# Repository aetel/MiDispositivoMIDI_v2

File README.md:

# Warning
This repository is no loger active. Everything has been moved to the BanaNut Electronics repository:
https://github.com/bananutelectronics

# MiDispositivoMIDI_v2
MiDispositivoMIDI is a DIY MIDI Controller developed by a couple students of the Polytechnic University of Madrid for a workshop given in May and October of 2014. The code is under MIT license and the hardware is under CC BY-NC-SA 4.0. Everything can be downloaded from this repository. If you are interested in helping us to improve our proyect, let us know!

# https://www.facebook.com/midispositivomidi
# midispositivomidi@gmail.com

# Hardware License
<br /><span xmlns:dct="http://purl.org/dc/terms/" property="dct:title">MiDispositivoMIDI</span> by <a xmlns:cc="http://creativecommons.org/ns#" href="https://github.com/midispositivomidi" property="cc:attributionName" rel="cc:attributionURL">Alvaro Lopez Revuelta & Pablo de Miguel Morales</a> is licensed under a <a rel="license" href="http://creativecommons.org/licenses/by-nc-sa/4.0/">Creative Commons Attribution-NonCommercial-ShareAlike 4.0 International License</a>.<br />Permissions beyond the scope of this license may be available at <a xmlns:cc="http://creativecommons.org/ns#" href="https://github.com/midispositivomidi" rel="cc:morePermissions">https://github.com/midispositivomidi</a>.

# Important notes
Note that this Arduino library also uses other libraries. You will need to download the following:
analogmuxdemux.h
SimpleTimer.h
Keypad.h
MIDI.h

# Features
This initial release has four examples in order to show the main features of the library. A brief explanation is given in the header of each example. Basically it shows how to light up the leds, send midi messages and use timmers.

# ChangeLog
-23rd February 2014, v2.0 initial release.

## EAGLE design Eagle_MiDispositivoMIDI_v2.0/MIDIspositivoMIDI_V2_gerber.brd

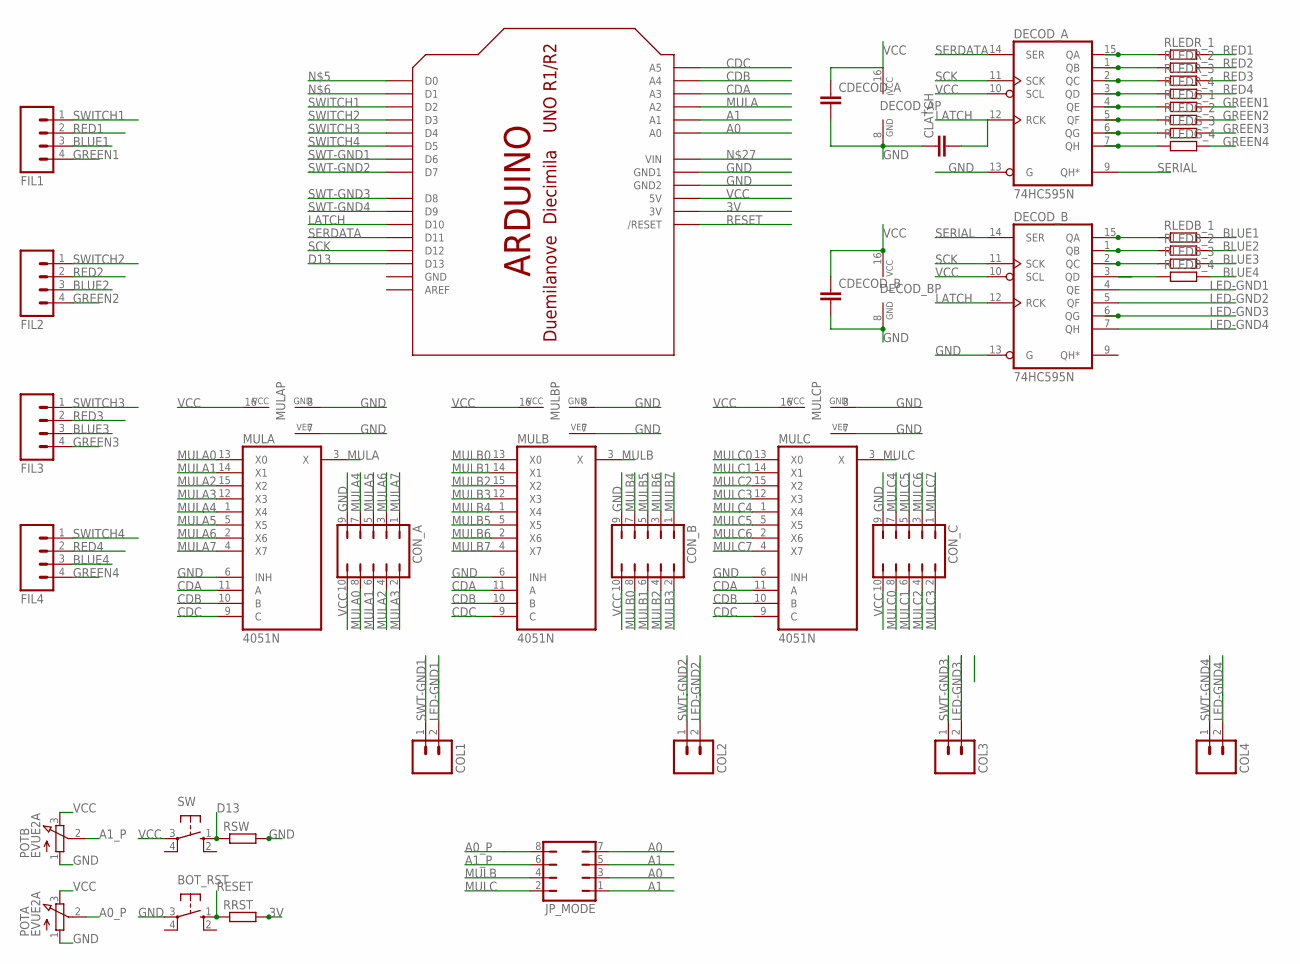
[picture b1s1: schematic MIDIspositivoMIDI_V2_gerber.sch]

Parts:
BOT_RST: 10-XX; B3F-10XX
CDECOD_A: C-EU025-030X050; C025-030X050
CDECOD_B: C-EU025-030X050; C025-030X050
CLATCH: C-EU025-030X050; C025-030X050
COL1, COL2, COL3, COL4: M02POLAR; MOLEX-1X2
CON_A: JP5Q
CON_B: JP5Q
CON_C: JP5Q
DECOD_A: 74HC595N; DIL16
DECOD_B: 74HC595N; DIL16
FIL1, FIL2, FIL3, FIL4: M04POLAR; MOLEX-1X4
JP_MODE: JP4Q
MULA: 4051N; DIL16
MULB: 4051N; DIL16
MULC: 4051N; DIL16
POTA: EVUE2A; EVUE
POTB: EVUE2A; EVUE
RLEDB_1, RLEDB_2, RLEDB_3, RLEDB_4: R-EU_0207/10; 0207/10
RLEDG_1, RLEDG_2, RLEDG_3, RLEDG_4: R-EU_0207/10; 0207/10
RLEDR_1, RLEDR_2, RLEDR_3, RLEDR_4: R-EU_0207/10; 0207/10
RRST: R-EU_0207/10; 0207/10
RSW: R-EU_0207/10; 0207/10
SW: 10-XX; B3F-10XX
U$1: ARDUINO-NOHOLE

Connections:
3V: RRST.2, U$1.3V
A0: JP_MODE.3, JP_MODE.7, U$1.A0
A0_P: JP_MODE.8, POTA.2 (S)
A1: JP_MODE.1, JP_MODE.5, U$1.A1
A1_P: JP_MODE.6, POTB.2 (S)
BLUE1: FIL1.3, RLEDB_1.2
BLUE2: FIL2.3, RLEDB_2.2
BLUE3: FIL3.3, RLEDB_3.2
BLUE4: FIL4.3, RLEDB_4.2
CDA: MULA.11 (A), MULB.11 (A), MULC.11 (A), U$1.A3
CDB: MULA.10 (B), MULB.10 (B), MULC.10 (B), U$1.A4
CDC: MULA.9 (C), MULB.9 (C), MULC.9 (C), U$1.A5
D13: RSW.1, SW.1 (S), U$1.D13
GND: BOT_RST.3, CDECOD_A.2, CDECOD_B.2, CLATCH.1, CON_A.9, CON_B.9, CON_C.9, DECOD_A.8 (GND), DECOD_A.13 (G), DECOD_B.8 (GND), DECOD_B.13 (G), MULA.6 (INH), MULA.7 (VEE), MULA.8 (GND), MULB.6 (INH), MULB.7 (VEE), MULB.8 (GND), MULC.6 (INH), MULC.7 (VEE), MULC.8 (GND), POTA.1 (A), POTB.1 (A), RSW.2, U$1.GND, U$1.GND1, U$1.GND2
GREEN1: FIL1.4, RLEDG_1.2
GREEN2: FIL2.4, RLEDG_2.2
GREEN3: FIL3.4, RLEDG_3.2
GREEN4: FIL4.4, RLEDG_4.2
LATCH: CLATCH.2, DECOD_A.12 (RCK), DECOD_B.12 (RCK), U$1.D10
LED-GND1: COL1.2, DECOD_B.4 (QE)
LED-GND2: COL2.2, DECOD_B.5 (QF)
LED-GND3: COL3.2, DECOD_B.6 (QG)
LED-GND4: COL4.2, DECOD_B.7 (QH)
MULA: MULA.3 (X), U$1.A2
MULA0: CON_A.8, MULA.13 (X0)
MULA1: CON_A.6, MULA.14 (X1)
MULA2: CON_A.4, MULA.15 (X2)
MULA3: CON_A.2, MULA.12 (X3)
MULA4: CON_A.7, MULA.1 (X4)
MULA5: CON_A.5, MULA.5 (X5)
MULA6: CON_A.3, MULA.2 (X6)
MULA7: CON_A.1, MULA.4 (X7)
MULB: JP_MODE.4, MULB.3 (X)
MULB0: CON_B.8, MULB.13 (X0)
MULB1: CON_B.6, MULB.14 (X1)
MULB2: CON_B.4, MULB.15 (X2)
MULB3: CON_B.2, MULB.12 (X3)
MULB4: CON_B.7, MULB.1 (X4)
MULB5: CON_B.5, MULB.5 (X5)
MULB6: CON_B.3, MULB.2 (X6)
MULB7: CON_B.1, MULB.4 (X7)
MULC: JP_MODE.2, MULC.3 (X)
MULC0: CON_C.8, MULC.13 (X0)
MULC1: CON_C.6, MULC.14 (X1)
MULC2: CON_C.4, MULC.15 (X2)
MULC3: CON_C.2, MULC.12 (X3)
MULC4: CON_C.7, MULC.1 (X4)
MULC5: CON_C.5, MULC.5 (X5)
MULC6: CON_C.3, MULC.2 (X6)
MULC7: CON_C.1, MULC.4 (X7)
unnamed: DECOD_A.15 (QA), RLEDR_1.1
unnamed: DECOD_A.1 (QB), RLEDR_2.1
unnamed: DECOD_A.2 (QC), RLEDR_3.1
unnamed: DECOD_A.3 (QD), RLEDR_4.1
unnamed: DECOD_A.4 (QE), RLEDG_1.1
unnamed: DECOD_A.5 (QF), RLEDG_2.1
unnamed: DECOD_A.6 (QG), RLEDG_3.1
unnamed: DECOD_A.7 (QH), RLEDG_4.1
unnamed: DECOD_B.15 (QA), RLEDB_1.1
unnamed: DECOD_B.1 (QB), RLEDB_2.1
unnamed: DECOD_B.2 (QC), RLEDB_3.1
unnamed: DECOD_B.3 (QD), RLEDB_4.1
RED1: FIL1.2, RLEDR_1.2
RED2: FIL2.2, RLEDR_2.2
RED3: FIL3.2, RLEDR_3.2
RED4: FIL4.2, RLEDR_4.2
RESET: BOT_RST.1 (S), RRST.1, U$1.RESET (/RESET)
SCK: DECOD_A.11 (SCK), DECOD_B.11 (SCK), U$1.D12
SERDATA: DECOD_A.14 (SER), U$1.D11
SERIAL: DECOD_A.9 (QH*), DECOD_B.14 (SER)
SWITCH1: FIL1.1, U$1.D2
SWITCH2: FIL2.1, U$1.D3
SWITCH3: FIL3.1, U$1.D4
SWITCH4: FIL4.1, U$1.D5
SWT-GND1: COL1.1, U$1.D6
SWT-GND2: COL2.1, U$1.D7
SWT-GND3: COL3.1, U$1.D8
SWT-GND4: COL4.1, U$1.D9
VCC: CDECOD_A.1, CDECOD_B.1, CON_A.10, CON_B.10, CON_C.10, DECOD_A.10 (SCL), DECOD_A.16 (VCC), DECOD_B.10 (SCL), DECOD_B.16 (VCC), MULA.16 (VCC), MULB.16 (VCC), MULC.16 (VCC), POTA.3 (E), POTB.3 (E), SW.3, U$1.5V

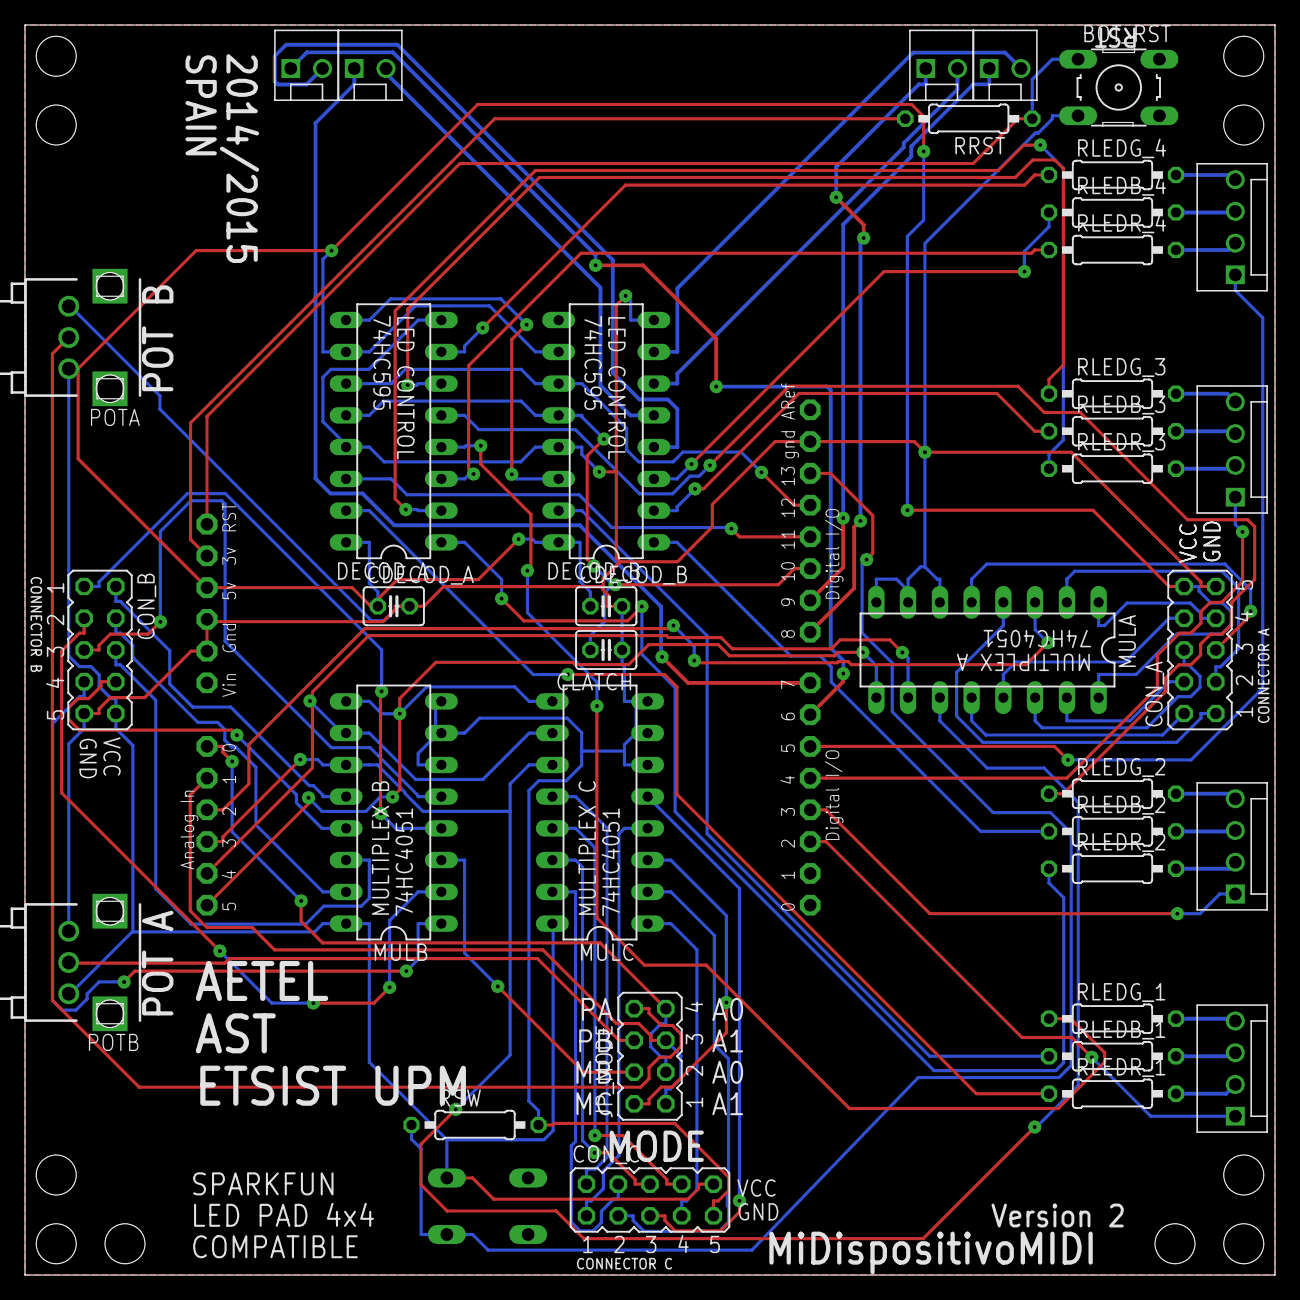
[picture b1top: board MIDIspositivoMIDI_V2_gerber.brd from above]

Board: 2 copper layers, 100.0 x 100.0 mm, 39 parts (1 on the bottom side), 79 nets.

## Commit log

2015-02-23 Initial Release
2015-02-23 Adding doc
2015-02-23 Guide Spanish
2015-02-23 names
2015-02-23 read me corrected
